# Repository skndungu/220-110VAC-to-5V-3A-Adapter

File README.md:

# 220-110VAC-to-5V-3A-Adapter
This repo contains a PCB design for a 220/110VAC to 5V 3A adapter for your 5V appliances and mobile phone for fast charging and powering

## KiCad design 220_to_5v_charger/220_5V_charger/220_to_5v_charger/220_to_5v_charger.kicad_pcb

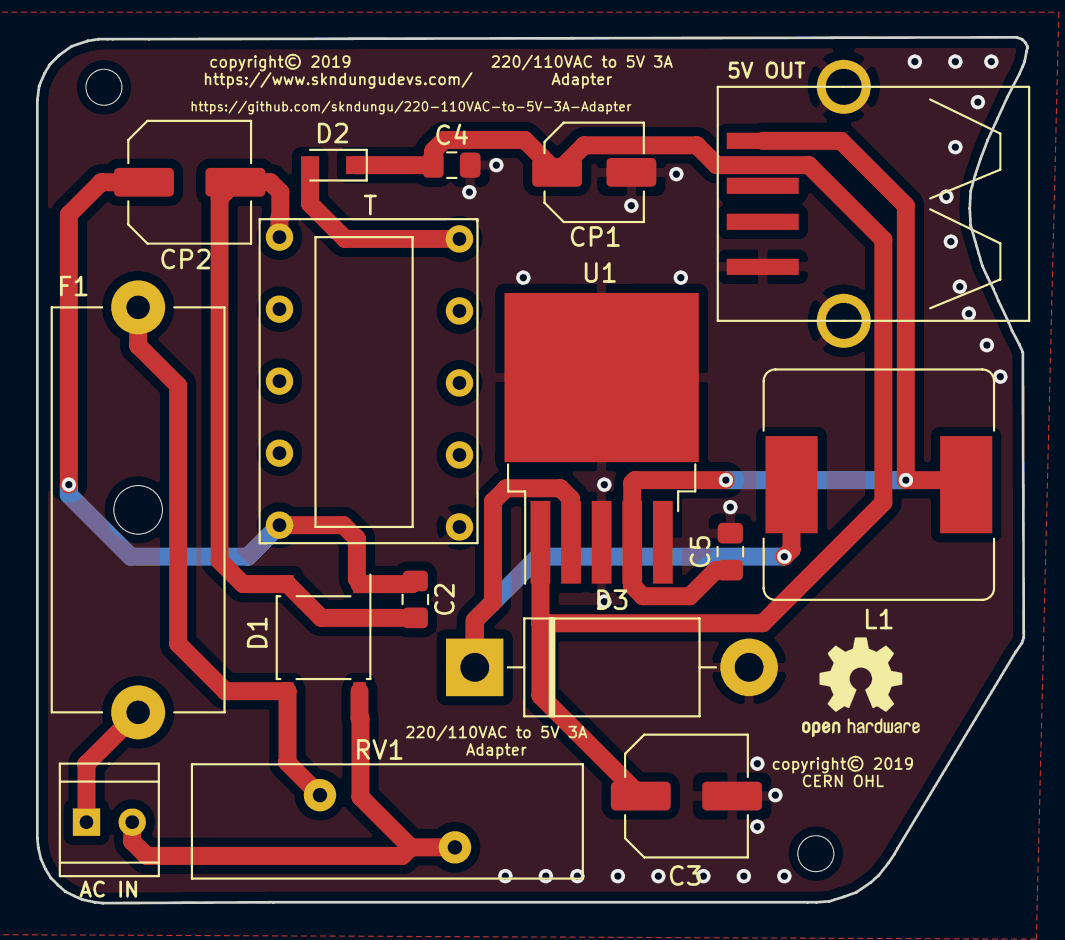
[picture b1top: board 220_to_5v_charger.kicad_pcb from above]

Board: 2 copper layers, 55.0 x 48.1 mm, 18 parts (0 on the bottom side), 10 nets.

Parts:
5V OUT: USB_A; PRT-09011
AC IN: Screw_Terminal_01x02; 39773-0002
C2: 10uF; C_0805_2012Metric_Pad1.15x1.40mm_HandSolder
C3: 680uF; C_Elec_6.3x7.7
C4: 0.1uF; C_0805_2012Metric_Pad1.15x1.40mm_HandSolder
C5: 220uF; C_0805_2012Metric_Pad1.15x1.40mm_HandSolder
CP1: 220uF; C_Elec_5x5.8
CP2: 470uF; C_Elec_6.3x7.7
D1: ABS10; Diode_Bridge_Diotec_ABS
D2: D; D_SOD-323_HandSoldering
D3: 1N5820; D_DO-201AD_P15.24mm_Horizontal
F1: Fuse; Fuseholder_Cylinder-5x20mm_Schurter_0031_8201_Horizontal_Op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
H1, H2: MountingHole; MountingHole_2mm
L1: 33uH; L_Bourns_SRR1260
RV1: Varistor; RV_Disc_D21.5mm_W6.1mm_P7.5mm
T: T; Transformer_EE22
U1: LM2596S-5; TO-263-5_TabPin3

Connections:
5V-OUT: 5V OUT.1, C5.1, L1.2, U1.4
/T1: C2.1, CP2.1, D1.1, T.1
/T4: C2.2, CP2.2, D1.2, T.5
/T6: D2.2, T.6
DC-OUT: C3.1, C4.1, CP1.1, D2.1, U1.1
GND: 5V OUT.4, 5V OUT.5, C3.2, C4.2, C5.2, CP1.2, D3.2, T.10, U1.3, U1.5
INA: D1.3, F1.1, RV1.1
INB: AC IN.2, D1.4, RV1.2
unnamed: D3.1, L1.1, U1.2
unnamed: AC IN.1, F1.2

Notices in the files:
220_to_5v_charger/220_5V_charger/220_to_5v_charger/220_to_5v_charger.kicad_pcb:
copyright© 2019
CERN OHL
